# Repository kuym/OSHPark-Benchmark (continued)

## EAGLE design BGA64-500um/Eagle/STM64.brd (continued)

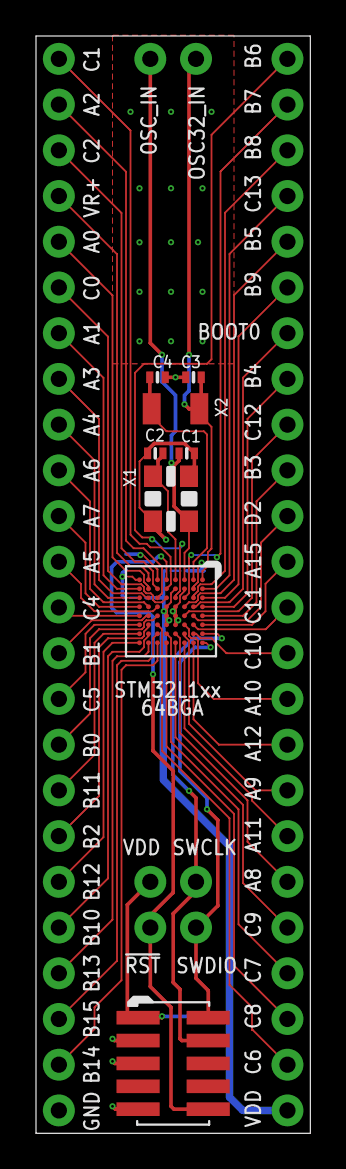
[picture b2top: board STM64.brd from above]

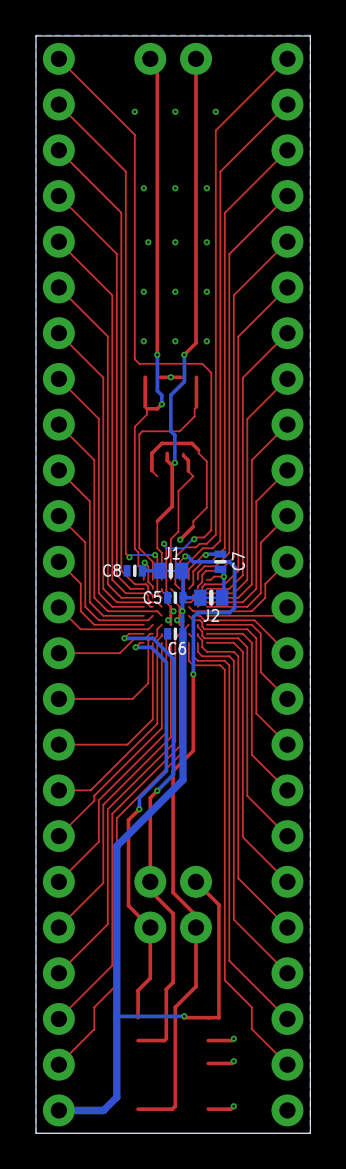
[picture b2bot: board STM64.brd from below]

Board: 2 copper layers, 15.2 x 61.0 mm, 22 parts (6 on the bottom side), 57 nets.

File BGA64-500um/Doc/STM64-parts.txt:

Partlist

Exported from STM64.sch at 04Mar16 12:30

EAGLE Version 7.2.0 Copyright (c) 1988-2014 CadSoft

Assembly variant: 

Part     Value                            Device                           Package                          Library  Sheet

C1                                        CAP-0402-MIN                     0402-MIN                         Outbreak 1
C2                                        CAP-0402-MIN                     0402-MIN                         Outbreak 1
C3                                        CAP-0402-MIN                     0402-MIN                         Outbreak 1
C4                                        CAP-0402-MIN                     0402-MIN                         Outbreak 1
C5                                        CAP-0402-MIN                     0402-MIN                         Outbreak 1
C6                                        CAP-0402-MIN                     0402-MIN                         Outbreak 1
C7                                        CAP-0402-MIN                     0402-MIN                         Outbreak 1
C8                                        CAP-0402-MIN                     0402-MIN                         Outbreak 1
IC1      ST-STM32L1XX-ARM-CORTEX-M3-64PIN ST-STM32L1XX-ARM-CORTEX-M3-64PIN BGA64-5X5MM-0.5MM                Outbreak 1
J1       JUMPER-0603-MIN                  JUMPER-0603-MIN                  0603-MIN-JUMPER                  Outbreak 1
J2       JUMPER-0603-MIN                  JUMPER-0603-MIN                  0603-MIN-JUMPER                  Outbreak 1
K1       HEADER-1X16-NO-SILK              HEADER-1X16-NO-SILK              HEADER-1X16-NO-SILK              Outbreak 1
K2       HEADER-1X16-NO-SILK              HEADER-1X16-NO-SILK              HEADER-1X16-NO-SILK              Outbreak 1
K3       HEADER-1X08-NO-SILK              HEADER-1X08-NO-SILK              HEADER-1X08-NO-SILK              Outbreak 1
K4       HEADER-1X08-NO-SILK              HEADER-1X08-NO-SILK              HEADER-1X08-NO-SILK              Outbreak 1
K5       HEADER-ARM-JTAG-2X5-1.27MM       HEADER-ARM-JTAG-2X5-1.27MM       HEADER-SMT-1.27MM-5X2-JTAG       Outbreak 1
K6       HEADER-1X02-0.1IN-NO-SILK        HEADER-1X02-0.1IN-NO-SILK        HEADER-1X02-NO-SILK              Outbreak 1
K7       HEADER-1X02-0.1IN-NO-SILK        HEADER-1X02-0.1IN-NO-SILK        HEADER-1X02-NO-SILK              Outbreak 1
K8       HEADER-1X01-NO-SILK              HEADER-1X01-NO-SILK              HEADER-1X01-NO-SILK              Outbreak 1
K9       HEADER-1X01-NO-SILK              HEADER-1X01-NO-SILK              HEADER-1X01-NO-SILK              Outbreak 1
X1       CRYSTAL-4-PIN-NDK-NX3225GA-MIN   CRYSTAL-4-PIN-NDK-NX3225GA-MIN   CRYSTAL-NDK-NX3225GA-3X2.5MM-MIN Outbreak 1
X2       CRYSTAL-1206                     CRYSTAL-1206                     1206-MIN                         Outbreak 1

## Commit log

2016-03-29 Added BGA64-500um design, 'STM64'
2019-02-05 Updated README.md and added L4 PCB design
